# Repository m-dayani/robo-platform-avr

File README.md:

# ROBO Platform | AVR Controller

The AVR microcontroller board is a component of the [Robo Platform project](https://github.com/m-dayani/robo-platform), which provides general-purpose inputs and outputs for a cell phone controller. Both hardware schematics and software are available.

This project is based on the [Obdev V-USB Library](https://www.obdev.at/products/vusb/index.html).

## Hardware

The hardware was initially designed for the [ATMEL ATmega8](https://www.microchip.com/en-us/product/ATMEGA8) AVR microcontroller using the Cadsoft Eagle (now [Autodesk Eagle](https://www.autodesk.com/products/eagle/free-download)).
Schematics and PCB layouts are available for SMD and TH (Through hole) technologies.

## Software

Based on the V-USB library, the algorithm handles USB interactions with an Android device (the [Robo Platform Android App](https://github.com/m-dayani/robo-platform-android)) and produces the required signals and commands.

The program is written in the C programming language and developed, compiled, and tested in [ATMEL AVR Studio 6.1](https://www.microchip.com/en-us/tools-resources/archives/avr-sam-mcus).

## Usage

The instructions to use this project are the same as any other Obdev V-USB project:

- Prepare the development board
- Implement your logic, link the library, and compile
- Upload the .hex file to the microcontroller
- You should also install an appropriate driver to connect the board to a desktop computer. This step can be skipped for connections to Android devices (using an OTG cable, Android auto-detects the device).

You can learn more about it in [this step-by-step tutorial](https://codeandlife.com/2012/01/22/avr-attiny-usb-tutorial-part-1/).

_WARNING_: Be careful with fuse bits when flashing your microcontroller in Linux (using Makefile). It is recommended you do not use `program` or `fuse` targets with `make`. If you upload the wrong fuse bits, your device might not work again.

## Troubleshooting

In case the board does not respond to USB commands:

- Check the connections
- Make sure the program is compiled for the right microcontroller (e.g. Atmega32)
- Make sure the frequency is correct (12MHz) and fuse bits are programmed correctly

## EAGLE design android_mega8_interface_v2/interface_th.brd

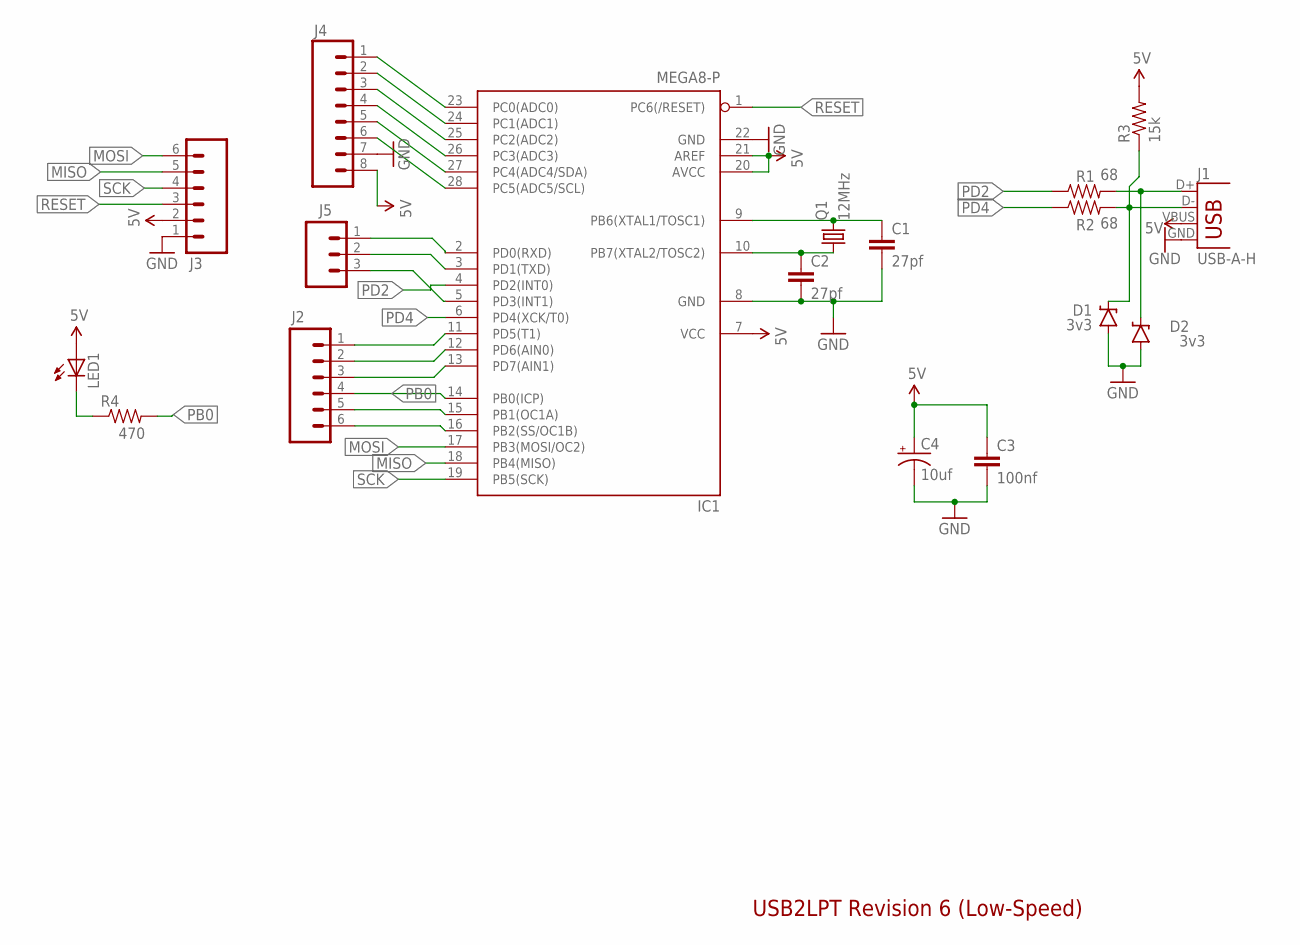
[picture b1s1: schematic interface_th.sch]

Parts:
C1, C2: 27pf; CAP-PTH-SMALL
C3: 100nf; CAP-PTH-SMALL
C4: 10uf; CPOL-RADIAL-10UF-25V
D1, D2: 3v3; DIODE-BZT52
IC1: MEGA8-P; DIL28-3
J1: USB-A-H
J2, J3: M06LONGPADS; 1X06_LONGPADS
J4: M08LONGPADS; 1X08_LONGPADS
J5: M03LONGPADS; 1X03_LONGPADS
LED1: LED3MM
Q1: 12MHz; HC49U-V
R1, R2: 68; AXIAL-0.3
R3: 15k; AXIAL-0.3
R4: 470; AXIAL-0.3

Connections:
5V: C3.1, C4.1 (+), IC1.7 (VCC), IC1.20 (AVCC), IC1.21 (AREF), J1.VBUS, J3.2, J4.8, LED1.A, R3.P$2 (2)
GND: C1.2, C2.2, C3.2, C4.2 (-), D1.A, D2.A, IC1.8 (GND), IC1.22 (GND), J1.GND, J3.1, J4.7
MISO: IC1.18 (PB4(MISO)), J3.5
MOSI: IC1.17 (PB3(MOSI/OC2)), J3.6
unnamed: LED1.K (C), R4.P$1 (1)
unnamed: IC1.11 (PD5(T1)), J2.1
unnamed: IC1.23 (PC0(ADC0)), J4.1
unnamed: C2.1, IC1.10 (PB7(XTAL2/TOSC2)), Q1.1
unnamed: C1.1, IC1.9 (PB6(XTAL1/TOSC1)), Q1.2
unnamed: D1.C, J1.D-, R2.P$2 (2), R3.P$1 (1)
unnamed: D2.C, J1.D+, R1.P$2 (2)
unnamed: IC1.24 (PC1(ADC1)), J4.2
unnamed: IC1.25 (PC2(ADC2)), J4.3
unnamed: IC1.26 (PC3(ADC3)), J4.4
unnamed: IC1.27 (PC4(ADC4/SDA)), J4.5
unnamed: IC1.28 (PC5(ADC5/SCL)), J4.6
unnamed: IC1.12 (PD6(AIN0)), J2.2
unnamed: IC1.13 (PD7(AIN1)), J2.3
unnamed: IC1.15 (PB1(OC1A)), J2.5
unnamed: IC1.16 (PB2(SS/OC1B)), J2.6
unnamed: IC1.2 (PD0(RXD)), J5.1
unnamed: IC1.3 (PD1(TXD)), J5.2
unnamed: IC1.5 (PD3(INT1)), J5.3
PB0: IC1.14 (PB0(ICP)), J2.4, R4.P$2 (2)
PD2: IC1.4 (PD2(INT0)), R1.P$1 (1)
PD4: IC1.6 (PD4(XCK/T0)), R2.P$1 (1)
RESET: IC1.1 (PC6(/RESET)), J3.3
SCK: IC1.19 (PB5(SCK)), J3.4

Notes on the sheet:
USB2LPT Revision 6 (Low-Speed)

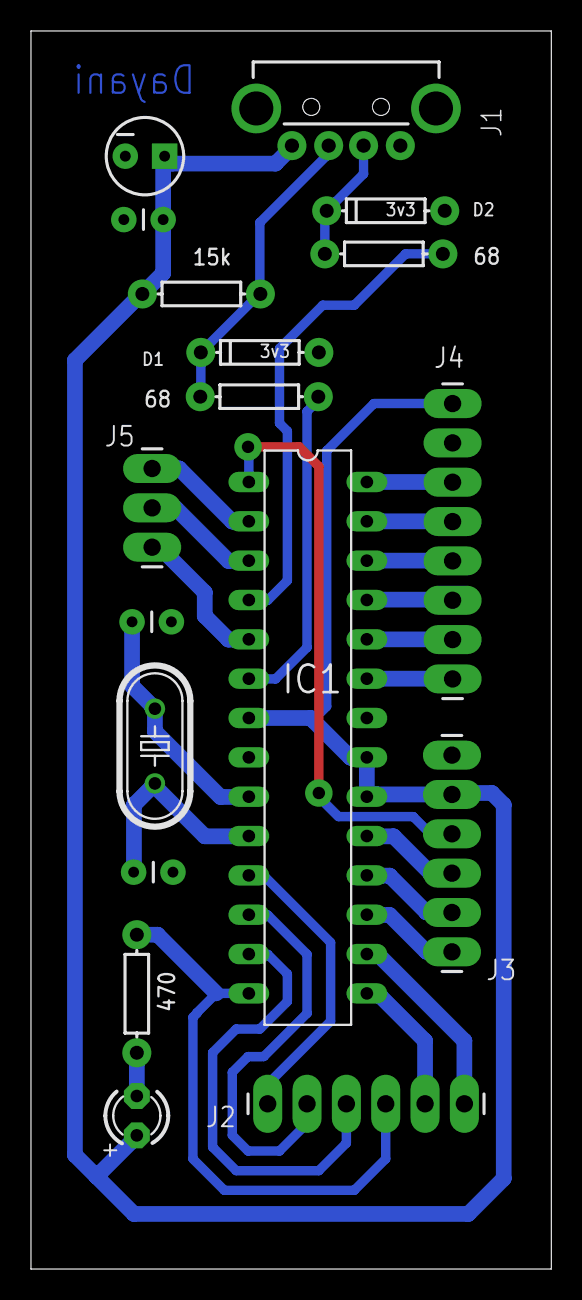
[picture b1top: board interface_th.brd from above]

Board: 2 copper layers, 33.6 x 79.9 mm, 18 parts (0 on the bottom side), 28 nets.

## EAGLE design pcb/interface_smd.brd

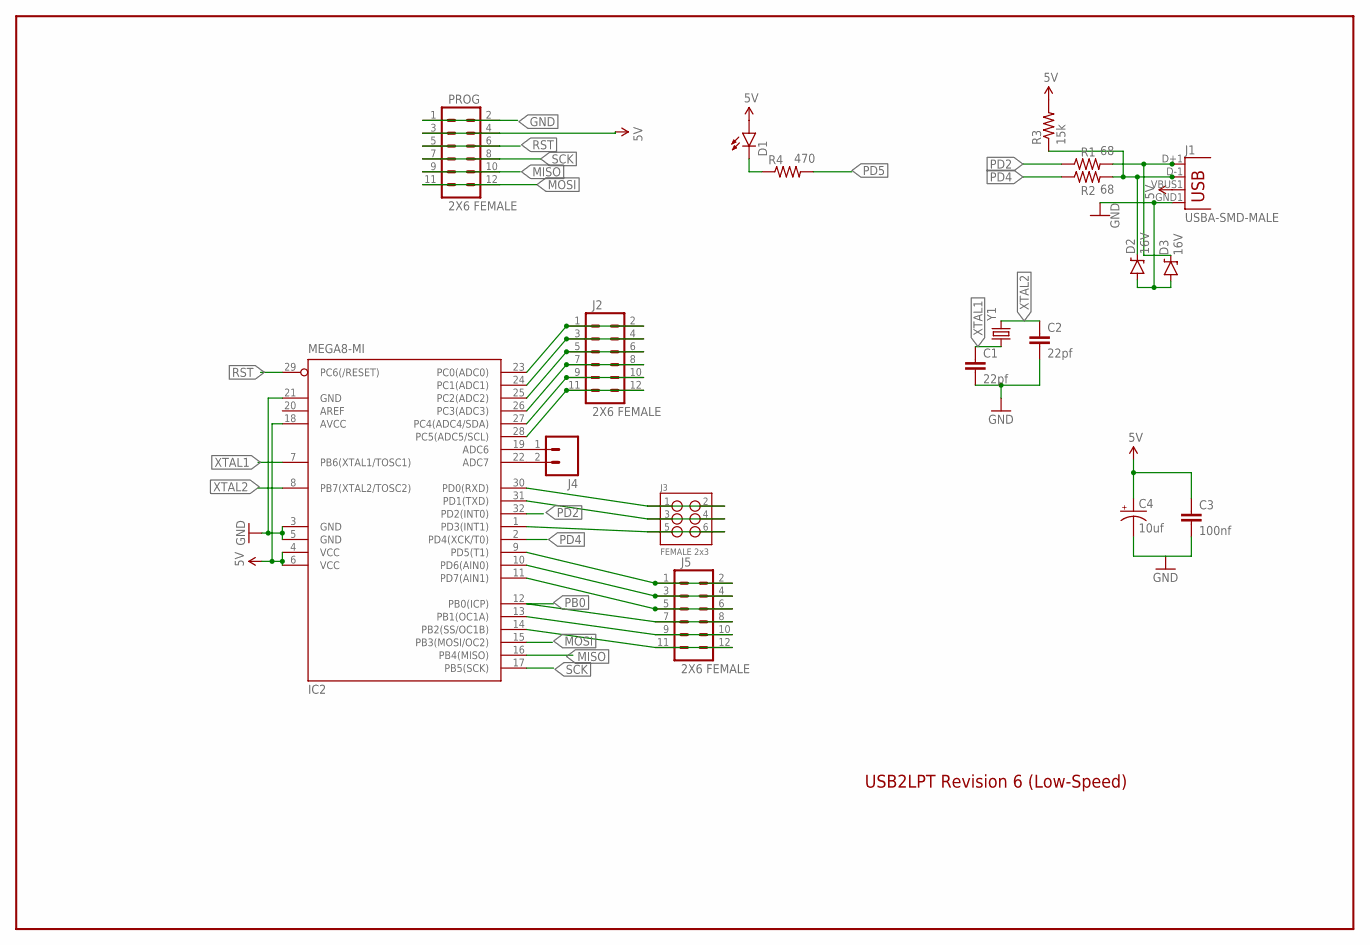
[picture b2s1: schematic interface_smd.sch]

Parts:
C1, C2: 22pf; 1206
C3: 100nf; 1206
C4: 10uf; EIA3216
D1: LED1206; LED-1206
D2, D3: 16V; SOD-123
IC2: MEGA8-MI; MLF32
J1: USBA-SMD-MALE; USB-A-SMT-MALE
J2, J5: 2X6 FEMALE; 2X6
J3: FEMALE 2x3; 2X3
J4: M02PTH; 1X02
PROG: 2X6 FEMALE; 2X6
R1, R2: 68; 1206
R3: 15k; 1206
R4: 470; 1206
Y1: CRYSTAL10.5X4.8; CRYSTAL-SMD-10.5X4.8-2PIN

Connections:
5V: C3.1, C4.A (+), D1.A, IC2.4 (VCC), IC2.6 (VCC), IC2.18 (AVCC), J1.VBUS1 (VBUS), PROG.3, PROG.4, R3.2
GND: C1.2, C2.2, C3.2, C4.C (-), D2.A, D3.A, IC2.3 (GND), IC2.5 (GND), IC2.21 (GND), J1.GND1 (GND), PROG.1, PROG.2
MISO: IC2.16 (PB4(MISO)), PROG.9, PROG.10
MOSI: IC2.15 (PB3(MOSI/OC2)), PROG.11, PROG.12
unnamed: D1.C, R4.1
unnamed: IC2.23 (PC0(ADC0)), J2.1, J2.2
unnamed: D3.C, J1.D+1 (D+), R1.2
unnamed: IC2.24 (PC1(ADC1)), J2.3, J2.4
unnamed: IC2.25 (PC2(ADC2)), J2.5, J2.6
unnamed: D2.C, J1.D-1 (D-), R2.2, R3.1
unnamed: IC2.26 (PC3(ADC3)), J2.7, J2.8
unnamed: IC2.27 (PC4(ADC4/SDA)), J2.9, J2.10
unnamed: IC2.28 (PC5(ADC5/SCL)), J2.11, J2.12
unnamed: IC2.19 (ADC6), J4.1
unnamed: IC2.22 (ADC7), J4.2
unnamed: IC2.30 (PD0(RXD)), J3.1, J3.2
unnamed: IC2.31 (PD1(TXD)), J3.3, J3.4
unnamed: IC2.1 (PD3(INT1)), J3.5, J3.6
unnamed: IC2.10 (PD6(AIN0)), J5.3, J5.4
unnamed: IC2.11 (PD7(AIN1)), J5.5, J5.6
unnamed: IC2.13 (PB1(OC1A)), J5.9, J5.10
unnamed: IC2.14 (PB2(SS/OC1B)), J5.11, J5.12
PB0: IC2.12 (PB0(ICP)), J5.7, J5.8
PD2: IC2.32 (PD2(INT0)), R1.1
PD4: IC2.2 (PD4(XCK/T0)), R2.1
PD5: IC2.9 (PD5(T1)), J5.1, J5.2, R4.2
RST: IC2.29 (PC6(/RESET)), PROG.5, PROG.6
SCK: IC2.17 (PB5(SCK)), PROG.7, PROG.8
XTAL1: C1.1, IC2.7 (PB6(XTAL1/TOSC1)), Y1.P$1 (1)
XTAL2: C2.1, IC2.8 (PB7(XTAL2/TOSC2)), Y1.P$2 (2)

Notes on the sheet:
USB2LPT Revision 6 (Low-Speed)

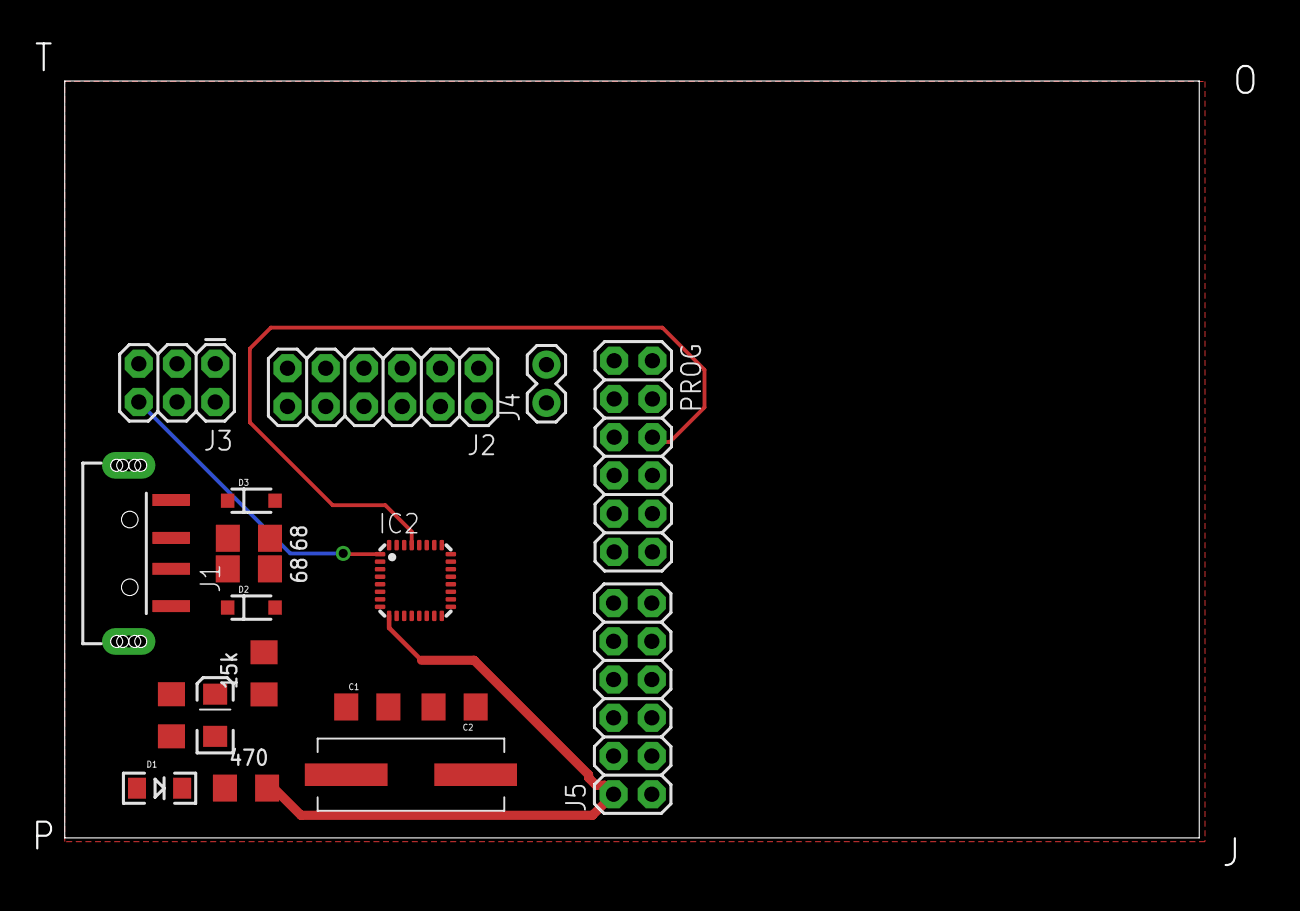
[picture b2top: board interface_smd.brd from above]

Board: 2 copper layers, 82.4 x 56.5 mm, 19 parts (0 on the bottom side), 30 nets.

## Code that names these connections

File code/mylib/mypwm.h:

#pragma once

#ifndef ARDUINO
#include <avr/io.h>
#include <avr/interrupt.h>
#else
#include <Arduino.h>
#endif

#ifndef ARDUINO
#ifndef uchar
#define uchar unsigned char
#endif
#else
typedef unsigned char uchar;
#endif

// A 50 Hz PWM pulse (20000 us)
// For a real servo or ESC:
// cnt_offset = 1415, max_cnt = 2815, max_cnt_cycle = 117
// For LED test (dimmer):
// cnt_offset = 0, max_cnt = 200, max_cnt_cycle = 200 (or 180)
extern unsigned short max_cnt_cycle;
extern unsigned short cnt_cycle;

extern unsigned short max_cnt;
extern unsigned short cnt_offset;
extern double max_time;
extern unsigned short max_time_int;

// 4 Channels for PWM Generation (to ESC)
// A: PB0, B: PB1, C: PB2, D: PB3
// Dynamic counters (changed in every loop)
extern unsigned long cnt_a, cnt_b, cnt_c, cnt_d;
// Max count determining duty cycle (changed with commands)
extern unsigned int cap_a, cap_b, cap_c, cap_d;
// Change max count based on the time of command
extern unsigned long t_a, t_b, t_c, t_d;

extern char state_a, state_b, state_c, state_d;
extern int n_cycle;

/* ==================================== Signal Gen (timer) ======================================== */

#ifdef __cplusplus
extern "C" {
#endif

void capUpdate(unsigned int *cap, const unsigned long t);

void capUpdateAll(void);

void timeCtrlUpdate(unsigned long *t, const uchar nb_p, const uchar nb_n, const uchar nsh_p, const uchar nsh_n);

void timeCtrlUpdateAll(void);

void pwmUpdate(const unsigned long cnt, const unsigned int cap, const uchar p_val);

void pwmUpdateAll(void);

void countUpdate(void);

void cycleUpdate(void);

#ifndef ARDUINO
void timerInit(void);
#endif


void set_timer(void);

char update_state(const uchar mask, const uchar n_bit);

void update_states(void);

void update_cnt(unsigned long* cnt, const char state);

#ifdef __cplusplus
}
#endif

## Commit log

2022-10-03 added ADC and linux support
2022-10-03 added linux version
2023-10-20 updated all files
2023-10-20 modified readme
2023-10-20 backed up several files
2024-05-03 6-channel car control and simple 1-ch flight control (experimental)
2024-05-31 completed quadcopter program, added arduino support for QC
2024-05-31 update removed files
2024-06-02 reorganized to support cmake generation
2024-06-21 modified Arduino's flight controller
2024-07-04 last cmake structure
2024-07-05 tested new efficient structure on Windows
2024-08-11 committing last changes, new library structure
2024-08-13 added comm_test and recording examples, improved vusb_wrapper
2024-08-13 updated comm_test and recording examples, improved vusb_wrapper
2024-08-14 finished comm test, corrected flight controller
2024-08-25 added a better Arduino flight controller (flight_controller_v2)

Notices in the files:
parts and their libraries:
SparkFun-Passives: Licensing: Creative Commons ShareAlike 4.0 International - https://creativecommons.org/licenses/by-sa/4.0
